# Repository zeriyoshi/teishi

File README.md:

# teishi
"Meishi" size experimental keyboard.

## changelog
**rev0**
- initial release.

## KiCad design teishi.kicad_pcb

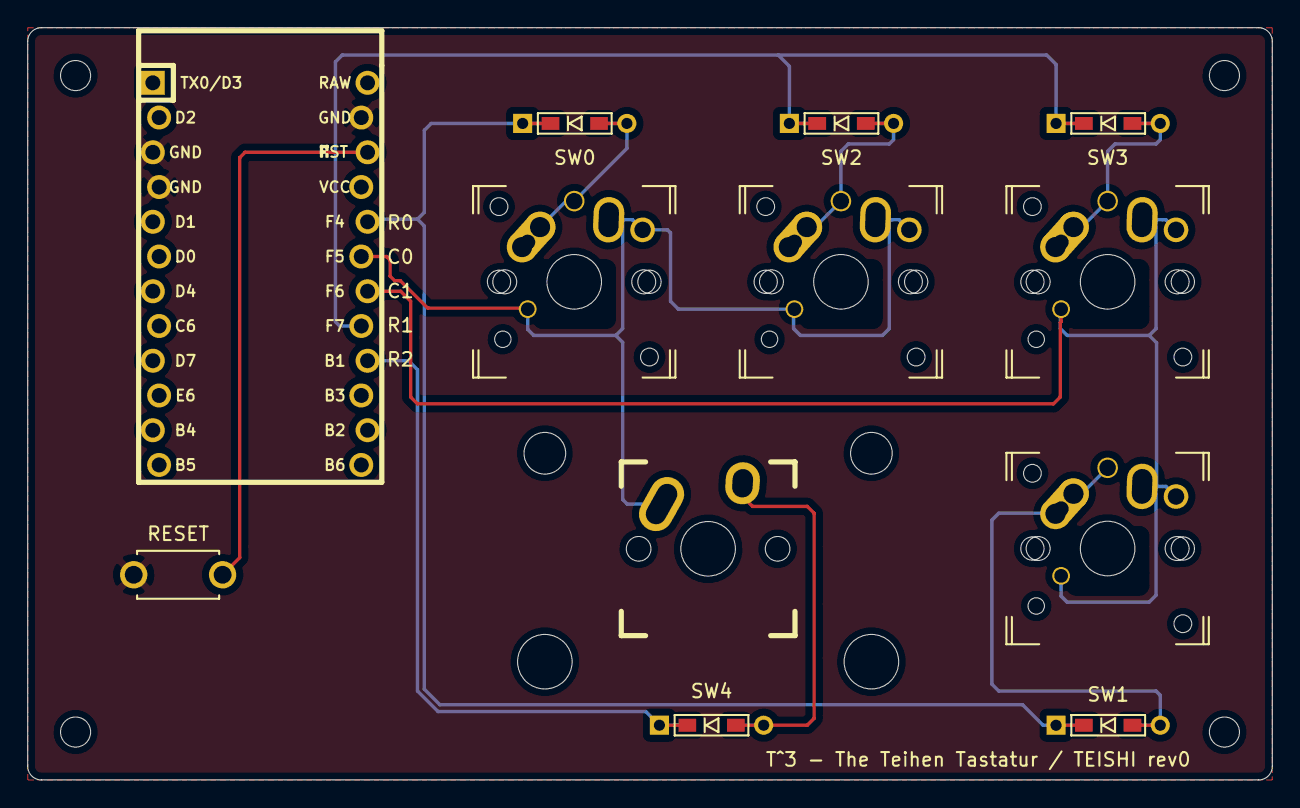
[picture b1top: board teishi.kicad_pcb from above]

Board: 2 copper layers, 91.0 x 55.0 mm, 12 parts (0 on the bottom side), 12 nets.

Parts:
D0, D1, D2, D3, D4: D; D3_TH_SMD
SW0, SW1, SW2, SW3: SW_Push; MX-ALPS-Choc-X-straight-oneside
SW4: SW_Push; Hybrid_PCB_200H
SW_RST1: SW_Push; ResetSW
U1: ProMicro; ArduinoProMicro-ZigZag

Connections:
COL0: SW0.1, SW2.1, SW4.1, U1.19
COL1: SW1.1, SW3.1, U1.18
GND: SW_RST1.2, U1.3, U1.4, U1.23
unnamed: D0.2, SW0.2
unnamed: D1.2, SW1.2
unnamed: D2.2, SW2.2
unnamed: D3.2, SW3.2
unnamed: D4.2, SW4.2
ROW0: D0.1, D1.1, U1.20
ROW1: D2.1, D3.1, U1.17
ROW2: D4.1, U1.16
RST: SW_RST1.1, U1.22

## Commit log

2020-06-20 initial commit.
